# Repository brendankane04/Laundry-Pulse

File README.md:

# Laundry-Pulse
Laundry Pulse is a simple & convenient button which when pressed will tell your roommates to move their things in a *pulse*!

Practically, this repository is composed of the code &amp; Schematics for a button which, when pressed, notifies all users that someone needs to remove their laundry from the machine. It can also be modified to send other messages with a convenient button press.

## Firmware

This file system is a project which can be conveniently opened in Atmel Studio 7 with the following important source files:

### Files

-**Error.c:** Error Messages & blinking \
-**ESP82_Drv.c:** Driver for the ESP-01 board which houses the ESP8266 chip. Allows communication between the main device & the external peripheral \
-**int.c:** Code for initializing & using an interrupt triggered on the button press \
-**main.c:** main file \
-**uart.c:** Initializes the UART peripheral & directs STDIO I/O toward UART

## Backend

This python script needs to be run on loop in a local server on the network

### Files

-**server.py:** Runs a local TCP server on the same network as the "Laundry Pulse" device

## Schematics

The schematics were made with KiCAD and can be viewed with any program which can edit .sch files.

### Files

**Schematics.sch:** The schematic listings for the whole project & can be edited \
**Schematics.pdf:** A PDF for readability

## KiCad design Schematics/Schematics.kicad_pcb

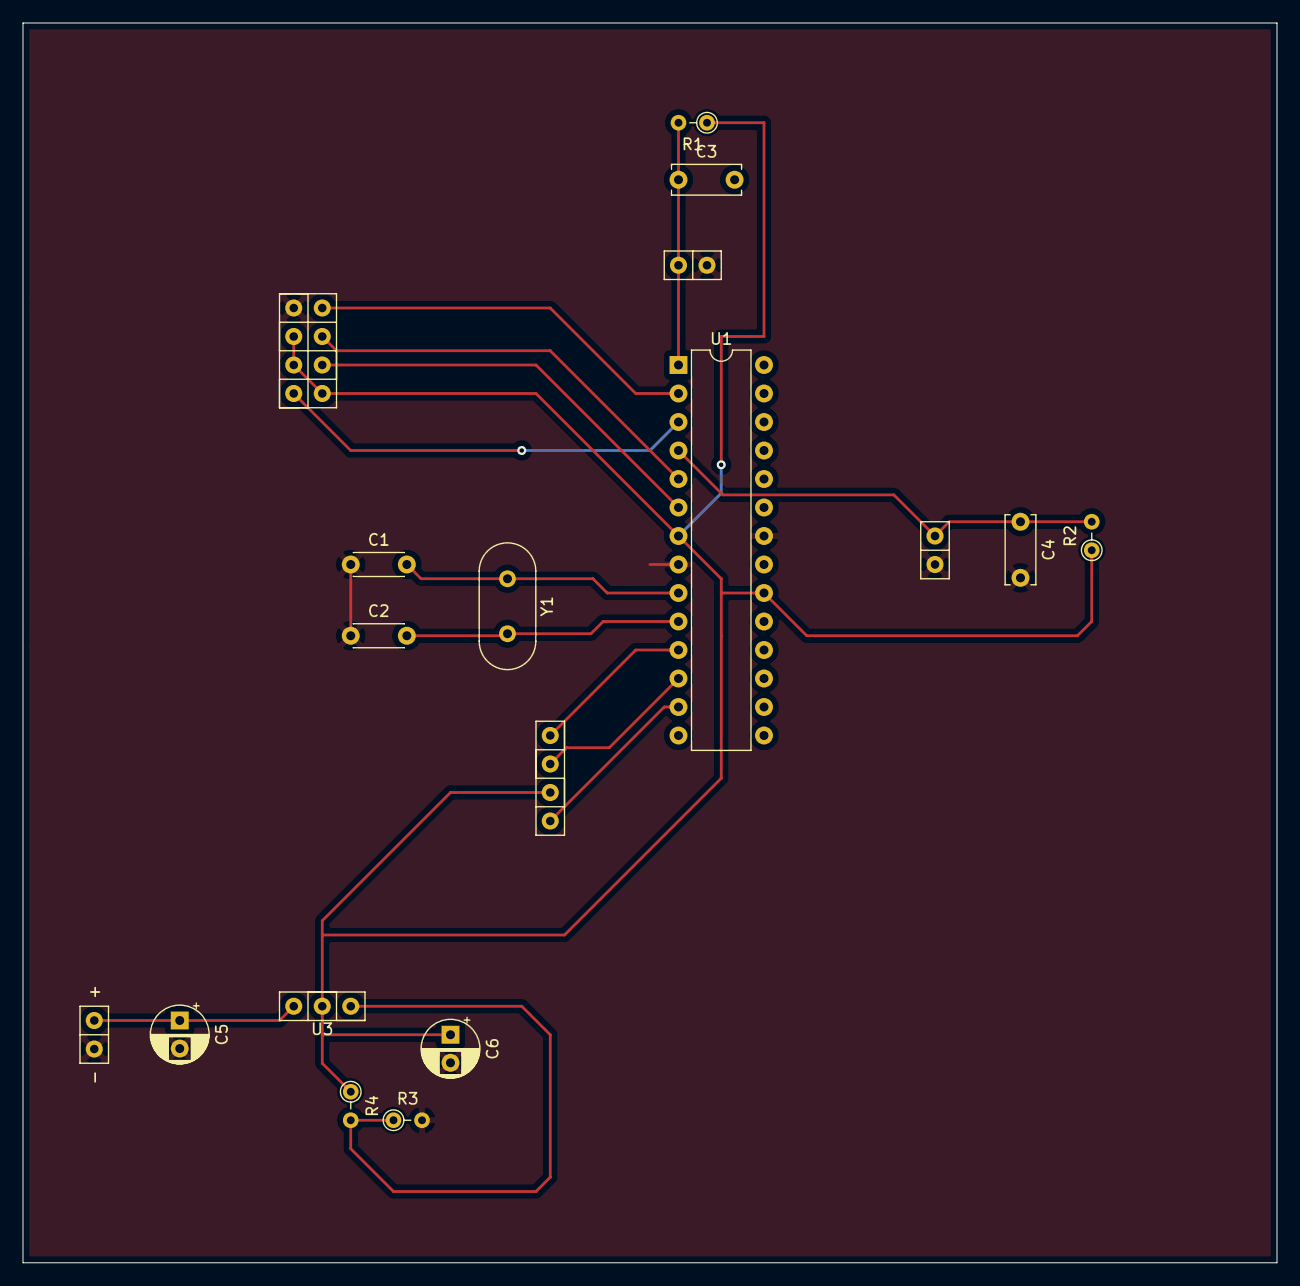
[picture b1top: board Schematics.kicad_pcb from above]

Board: 2 copper layers, 111.8 x 110.5 mm, 18 parts (0 on the bottom side), 15 nets.

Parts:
BT1: Battery_Cell; Connector_Battery
C1, C2: 22pF; C_Disc_D4.3mm_W1.9mm_P5.00mm
C3, C4: 0.1uF; C_Disc_D6.0mm_W2.5mm_P5.00mm
C5, C6: 0.1uF; CP_Radial_D5.0mm_P2.50mm
D1: LED_BGAR; Connector_LED
R1, R2: 10k; R_Axial_DIN0204_L3.6mm_D1.6mm_P2.54mm_Vertical
R3: 390; R_Axial_DIN0204_L3.6mm_D1.6mm_P2.54mm_Vertical
R4: 240; R_Axial_DIN0204_L3.6mm_D1.6mm_P2.54mm_Vertical
SW1, SW2: SW_Push; Connector_Button
U1: ATmega328P-PU; DIP-28_W7.62mm
U2: ESP-01; ESP01_Footprint
U3: LM317; LM317_Custom
Y1: Crystal; Crystal_HC18-U_Vertical

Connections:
+3V3: C6.1, D1.3, R1.1, R2.1, R4.1, U1.7, U1.20, U2.2, U2.3, U2.5, U3.2
/CH_PD: U1.5, U2.7
/INT0: C4.1, R2.2, SW2.1, U1.4
/REST: U1.6, U2.6
/RX: U1.2, U2.8
/TX: U1.3, U2.4
GND: BT1.2, C1.1, C2.1, C4.2, C5.2, C6.2, R3.2, SW1.2, SW2.2, U1.8, U1.22, U2.1
unnamed: BT1.1, C5.1, U3.3
unnamed: C1.2, U1.9, Y1.1
unnamed: C2.2, U1.10, Y1.2
unnamed: C3.1, R1.2, SW1.1, U1.1
unnamed: D1.1, U1.11
unnamed: D1.2, U1.12
unnamed: D1.4, U1.13
unnamed: R3.1, R4.2, U3.1

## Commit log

2021-05-18 A superfluous TODO was removed.
2021-05-18 The README was written.
2021-05-18 A typo in the README was fixed.
2021-05-22 Error checking was added to the ESP driver.
2021-05-23 The schematics were added.
2021-05-23 A PDF of the schematic was added. The README was also altered.
2021-05-23 The README was edited.
2021-05-25 The schematics were altered. A Circuit board layout was added.
2021-05-25 The PDFs of the schematics were changed. The libraries were also streamlined.
2021-06-04 A picture of the final, physical circuit was added.
2021-06-04 The file type of the image was changed.
2021-06-22 Final product pictures were added.
2021-07-26 Debug was removed.
2021-07-26 .vs was removed.
2021-08-05 Library changes were made.
2021-08-19 README update
